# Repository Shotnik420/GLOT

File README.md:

# ✈️ GLOT - Kontroler Lotu RC

GLOT to projekt, którego celem jest stworzenie kontrolera lotu dla samolotów RC z możliwie jak najlepszym stosunkiem jakości do ceny.

Jest to projekt głównie do naukii podstaw awioniki jak i tworzenia systemów opartych na STM32 i jak radzą sobie w trudnych warunkach.

---

## Wersje
- 📦 **[GLOT v1.0 / 1.5 (Najlepiej udokumentowana)](https://github.com/Shotnik420/GLOT/tree/main/Versions/GLOT%20v1.0)**  
  _Wersja prototypowa._ Pierwsze kroki i weryfikacja koncepcji. Zakończona sukcesem w postaci pierwszego, kilkusekundowego lotu. Pozwoliła zidentyfikować kluczowe problemy z zasilaniem (brownouty), zakłóceniami magistrali I2C i gabarytami płytek. Składała się z dedykowanego nadajnika na ESP32 i odbiornika na STM32.
- ⚡ **[GLOT v2.0 (Obecna wersja)](https://github.com/Shotnik420/GLOT/tree/main/Versions/GLOT%20v2.0)**  
  _Rozwój i optymalizacja._ Najnowsza generacja kontrolera, w której wyciągnięto wnioski z błędów poprzednika. Zoptymalizowano kwestie zasilania serwomechanizmów, poprawiono routing ścieżek na PCB i zmniejszono rozmiary urządzenia, aby lepiej pasowało do ciasnych kadłubów modeli RC.

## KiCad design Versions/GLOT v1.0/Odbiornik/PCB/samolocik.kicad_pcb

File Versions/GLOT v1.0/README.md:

# GLOT 1.0 / 1.5

Wersja startowa i pierwsze kroki postawione w kierunku stworzenia w pełni funkcjonalnego prototypu. Pomimo błędów wieku dziecięcego, platformę udało się uruchomić fizycznie, co zaowocowało udanym lotem trwającym 7-8 sekund. Połączyłem wersje 1.0 i 1.5 w jedną sekcję, ponieważ jedyną różnicą między nimi jest płytka PCB, która otrzymała kilka poprawek, kod pozostaje identyczny.

Zdecydowałem się na stworzenie autorskiego nadajnika i odbiornika, aby ominąć koszty drogiej aparatury RC (co dla budżetu studenta jest kluczowe). Projekt podzielił się na dwa moduły:

- **Odbiornik:** Zbudowany na bazie płytki STM32 Blackpill z układem STM32F411CEU6. Moduł nRF24L01+PA+LNA odbiera dane i tłumaczy je na wysterowanie 4 serwomechanizmów oraz prędkość silnika bezszczotkowego (ESC). Na pokładzie znajduje się moduł GY-91 (MPU9250), obsługiwany przez prowizoryczny system PID stabilizujący lot.

- **Nadajnik:** Oparty na ESP32-S3. Wykorzystuje bibliotekę Bluepad32 do łączenia się z kontrolerem od konsoli przez Bluetooth, a wejścia przesyła w świat za pomocą modułu nRF24L01+PA+LNA. Decyzja o użyciu tak potężnego mikrokontrolera i sporych komponentów z tzw. "szuflady" sprawiła, że układ stał się dość masywny.

---

## Użyte technologie

| Technologia / Komponent | Opis i zastosowanie w projekcie                                                                 |
| :---------------------- | :---------------------------------------------------------------------------------------------- |
| **C / STM32 HAL**       | Główny język i biblioteka sprzętowa użyta do zaprogramowania mikrokontrolera STM32.             |
| **I2C**                 | Protokół komunikacyjny użyty do odczytu danych z modułu GY-91 (akcelerometr/żyroskop).          |
| **SPI**                 | Szybka magistrala użyta do obsługi modułu radiowego nRF24L01+PA+LNA.                            |
| **PWM (Timery)**        | Sprzętowe generowanie sygnałów (TIM2, TIM3) sterujących serwami i silnikiem bezszczotkowym.     |
| **USB CDC**             | Wirtualny port COM (USB) wykorzystany do wygodnego przesyłania logów i debugowania.             |
| **Algorytm PID**        | Regulator (Proporcjonalno-Całkująco-Różniczkujący) wyliczający korekty lotek i steru wysokości. |

---

## Podsumowanie testów

### Odbiornik

### Co poszło dobrze

- Pisanie kodu w .C dla STM'a okazało się zaskakująco proste i przyjemne. Stworzyłem całkiem dobry system, który posiadał odbieranie danych radiowych i przekazywanie dostarczonych wartości na zakres serw. Jest prowizoryczny PID (Prioporcjonalno-całkująco-różniczkujący), który jednak jest tak skomplikowany że nie przyznam się do jego napisania, a zawdzięczam go Gemini od Google'a, lecz jest to jeden z moich celów na następne wersje by go zrozumieć i napisać raz jeszcze.

### Co poszło ŹLE

- Połączenie prądu serw z prądem układu sterowniczego. STM32 brownoutował za każdym mocniejszym pociągnieciem serwa. Wymagało przecięcia ścieżek i dolutowania osobnej baterii.

- Pomylone ścieżki SDA i SCL dla modułu GY-91. Wymagało przeciecia ścieżek i zrobienia zworek.

- Zbyt słaby prąd dla serw. Uruchomienie wszystkich naraz było niemożliwe.

- Rozmiar płytki był wyraźnie niekorzystny dla budowy samolotu. Za duży.

- Niezabezpieczenie układów przed wsadzeniem ich do ciasnego kokpitu pojazdu spowodowało fizyczne zwarcie i spalenie mikrokontrolera i przetwornicy

### Nadajnik

### Co poszło ŹLE

- Użycie komponentów będących tzw. "pod ręką" przez co płytka nadajnika jest niepotrzebnie duża. Duże przyciski, duży moduł przetwornicy, duży mikrokontroler.

- Dodanie pól na przyciski, których nie musiało tam być bo kontroler realizował wszystkie potrzeby wejścia.

- Pomimo faktu że zrobienie nadajnika na podstawie kontrolera do Xboxa wydawało się fajnym pomysłem to faktyczna realizacja trochę zniechęciła mnie do tej wizji. Częste zerwania połączeń, zmiany bibliotek, zacinający się cały esp32. Zastanowie się nad kupnem faktycznego kontrolera w przyszłości.

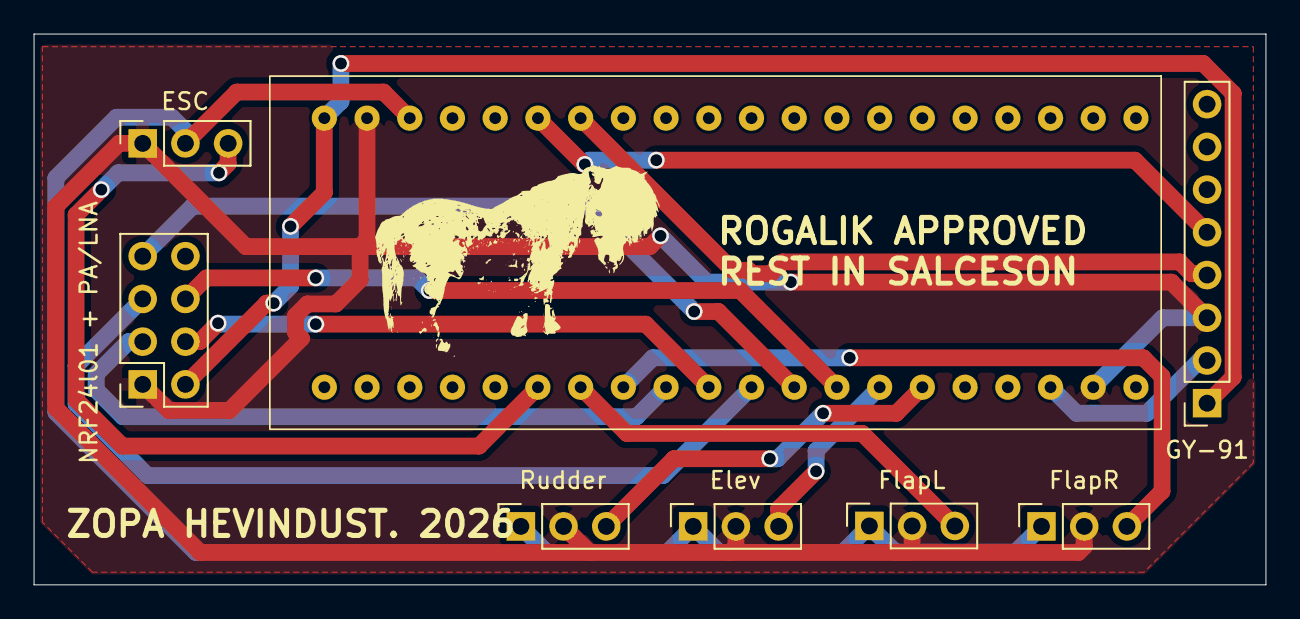
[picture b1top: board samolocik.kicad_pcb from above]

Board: 2 copper layers, 73.2 x 32.8 mm, 8 parts (0 on the bottom side), 16 nets.

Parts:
ESC: ESC; PinSocket_1x03_P2.54mm_Vertical
Elev: SerwoElev; PinSocket_1x03_P2.54mm_Vertical
FlapL: SerwoFlapL; PinSocket_1x03_P2.54mm_Vertical
FlapR: SerwoFlapR; PinSocket_1x03_P2.54mm_Vertical
GY-91: GY-91; PinSocket_1x08_P2.54mm_Vertical
NRF24l01 + PA/LNA: Conn_02x04_Odd_Even; PinSocket_2x04_P2.54mm_Vertical
Rudder: SerwoRudder; PinSocket_1x03_P2.54mm_Vertical
STM32BLACKPILL1: stm32

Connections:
GND: ESC.1, Elev.2, FlapL.2, FlapR.2, GY-91.3, NRF24l01 + PA/LNA.1, Rudder.2, STM32BLACKPILL1.4 (G), STM32BLACKPILL1.37 (G)
unnamed: GY-91.1, NRF24l01 + PA/LNA.2, STM32BLACKPILL1.39 (3V3)
unnamed: NRF24l01 + PA/LNA.3, STM32BLACKPILL1.24 (A3)
unnamed: NRF24l01 + PA/LNA.4, STM32BLACKPILL1.22 (A4)
unnamed: NRF24l01 + PA/LNA.5, STM32BLACKPILL1.20 (A5)
unnamed: NRF24l01 + PA/LNA.6, STM32BLACKPILL1.16 (A7)
unnamed: NRF24l01 + PA/LNA.7, STM32BLACKPILL1.18 (A6)
unnamed: GY-91.2, STM32BLACKPILL1.6 (3V3)
unnamed: GY-91.4, STM32BLACKPILL1.27 (B6)
unnamed: GY-91.5, STM32BLACKPILL1.29 (B7)
unnamed: ESC.2, Elev.1, FlapL.1, FlapR.1, Rudder.1, STM32BLACKPILL1.35 (5V)
unnamed: ESC.3, STM32BLACKPILL1.30 (A0)
unnamed: Rudder.3, STM32BLACKPILL1.12 (B1)
unnamed: Elev.3, STM32BLACKPILL1.14 (B0)
unnamed: FlapL.3, STM32BLACKPILL1.28 (A1)
unnamed: FlapR.3, STM32BLACKPILL1.26 (A2)

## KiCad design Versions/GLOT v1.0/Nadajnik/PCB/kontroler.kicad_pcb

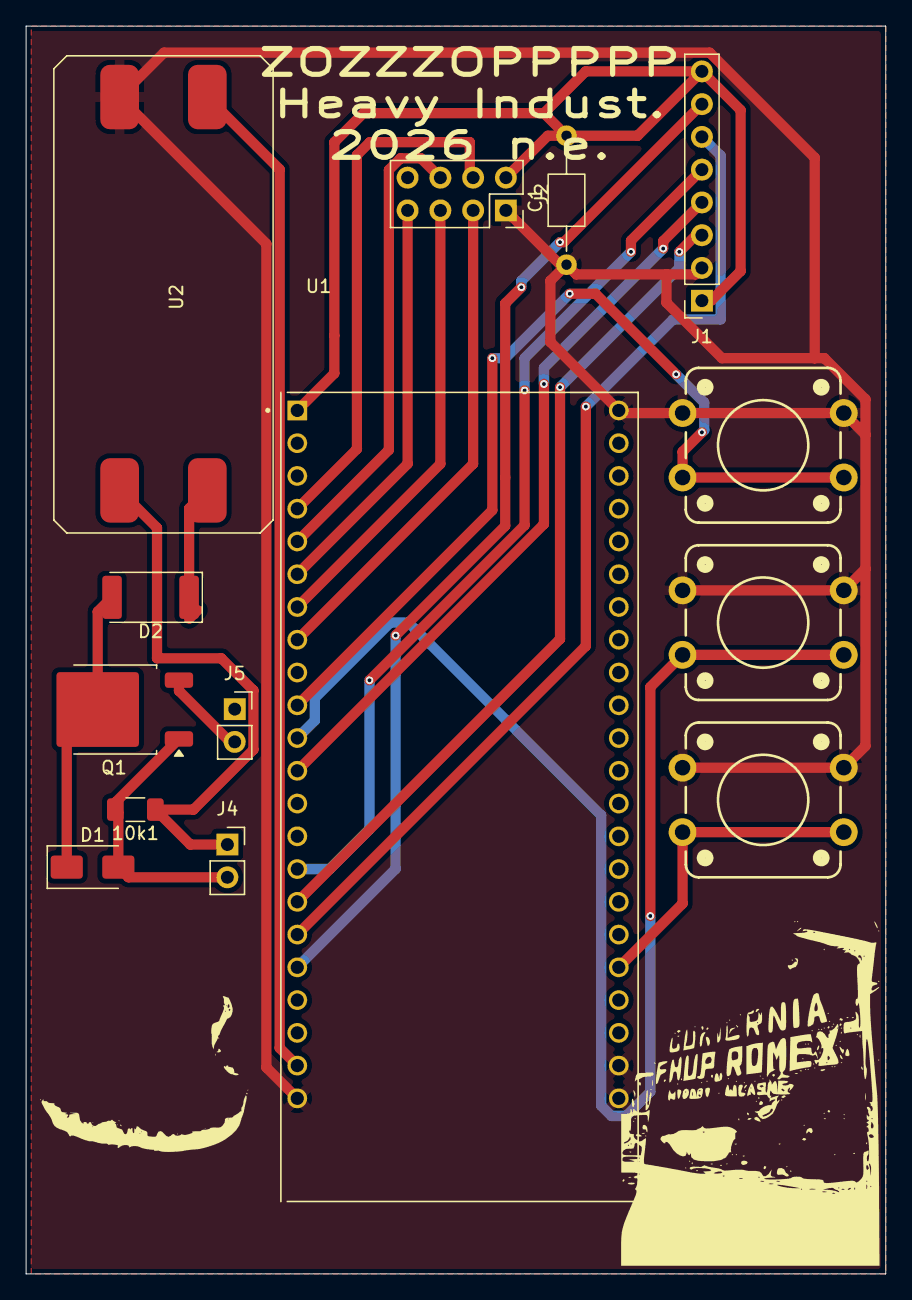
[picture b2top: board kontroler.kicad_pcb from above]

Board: 2 copper layers, 66.7 x 96.8 mm, 14 parts (0 on the bottom side), 21 nets.

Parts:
10k1: R; R_1206_3216Metric_Pad1.30x1.75mm_HandSolder
C1: C; C_Axial_L3.8mm_D2.6mm_P10.00mm_Horizontal
D1: SS24; D_SMA
D2: Red; LED_2512_6332Metric_Pad1.52x3.35mm_HandSolder
J1: ekran; PinSocket_1x08_P2.54mm_Vertical
J2: NRF24; PinSocket_2x04_P2.54mm_Vertical
J4: HW-373 OUT; PinSocket_1x02_P2.54mm_Vertical
J5: HW-373 B; PinSocket_1x02_P2.54mm_Vertical
Q1: IRFR9020; TO-252-2
SW1: btn1; Push_PTH_12x12mm
SW2: btn2; Push_PTH_12x12mm
SW3: btn3; Push_PTH_12x12mm
U1: ESP32-S3-DEVKITC-1-N8R2; ESPS3WIDE
U2: hw-045

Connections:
3V3: C1.2, J1.1, J1.8, J2.2, U1.J1_1 (3V3), U1.J1_2 (3V3)
GND: C1.1, J1.2, J2.1, SW1.1, SW2.1, SW3.1, U1.J1_22 (GND), U1.J3_1 (GND), U1.J3_21 (GND), U1.J3_22 (GND), U2.3 (VOUT-)
unnamed: 10k1.2, D1.2 (A), J4.2, Q1.1 (G)
unnamed: D1.1 (K), D2.2 (A), Q1.2 (D)
unnamed: D2.1 (K), U2.1 (VIN+)
unnamed: J1.3, U1.J1_16 (GPIO10)
unnamed: J1.4, U1.J1_12 (GPIO8)
unnamed: J1.5, U1.J1_15 (GPIO9)
unnamed: J1.6, U1.J1_17 (GPIO11)
unnamed: J1.7, U1.J1_18 (GPIO12)
unnamed: J2.3, U1.J1_8 (GPIO15)
unnamed: J2.4, U1.J1_4 (GPIO4)
unnamed: J2.5, U1.J1_7 (GPIO7)
unnamed: J2.6, U1.J1_5 (GPIO5)
unnamed: J2.7, U1.J1_6 (GPIO6)
unnamed: 10k1.1, J4.1, U2.2 (VIN-)
unnamed: J5.2, Q1.3 (S)
unnamed: U1.J1_21 (5V0), U2.4 (VOUT-)
unnamed: SW1.2, U1.J1_10 (GPIO17)
unnamed: SW2.2, U1.J1_11 (GPIO18)
unnamed: SW3.2, U1.J3_18 (GPIO21)
